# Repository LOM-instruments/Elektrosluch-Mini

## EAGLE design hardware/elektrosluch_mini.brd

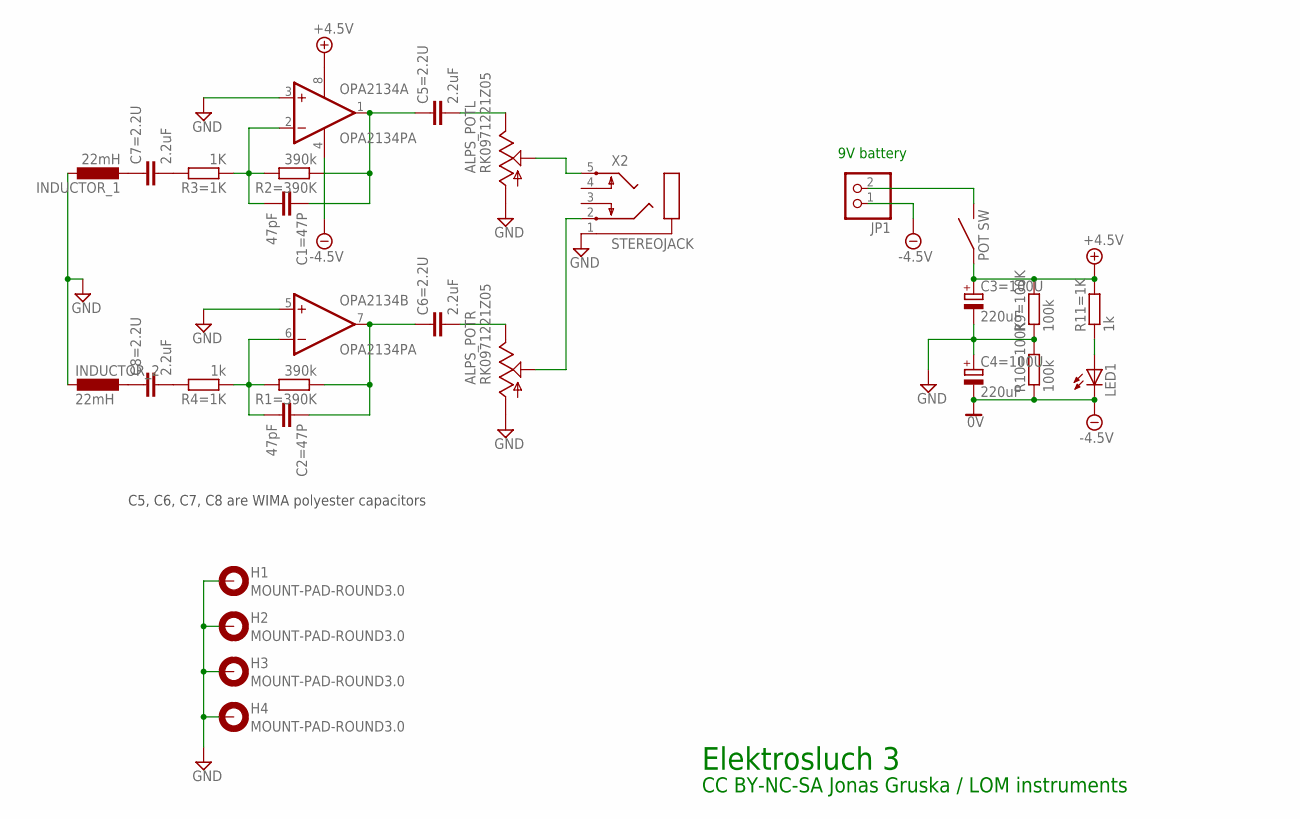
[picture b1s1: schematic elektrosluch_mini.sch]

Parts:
ALPS_POT: RK0971221Z05; ALPS_RK0971221Z0X
C1=47P, C2=47P: 47pF; C050-024X044
C3=100U, C4=100U: 220uF; E2,5-5
C5=2.2U, C6=2.2U, C7=2.2U, C8=2.2U: 2.2uF; WIMA10UF
H1, H2, H3, H4: MOUNT-PAD-ROUND3.0; 3,0-PAD
INDUCTOR_1, INDUCTOR_2: 22mH; COIL
JP1: PINHD-1X2; 1X02
LED1: LED3MM
OPA2134: OPA2134PA; DIL08
R1=390K, R2=390K: 390k; 0207/10
R3=1K: 1K; 0207/10
R4=1K, R11=1K: 1k; 0207/10
R9=100K, R10=100K: 100k; 0207/10
X2: STEREOJACK; STX3100

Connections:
+5V: ALPS_POT.S1, C3=100U.+, OPA2134.8 (V+), R9=100K.2, R11=1K.2
-5V: C4=100U.-, JP1.1, LED1.K (C), OPA2134.4 (V-), R10=100K.1
GND: ALPS_POT.G1 (1), ALPS_POT.G2 (1), C3=100U.-, C4=100U.+, H1.B3,0, H2.B3,0, H3.B3,0, H4.B3,0, INDUCTOR_1.P$1 (1), INDUCTOR_2.P$2 (2), OPA2134.3 (+IN), OPA2134.5 (+IN), R9=100K.1, R10=100K.2, X2.1
unnamed: C1=47P.2, OPA2134.2 (-IN), R2=390K.2, R3=1K.1
unnamed: C1=47P.1, C5=2.2U.P$1 (1), OPA2134.1 (OUT), R2=390K.1
unnamed: ALPS_POT.I1 (3), C5=2.2U.P$2 (2)
unnamed: C2=47P.2, OPA2134.6 (-IN), R1=390K.2, R4=1K.1
unnamed: C2=47P.1, C6=2.2U.P$1 (1), OPA2134.7 (OUT), R1=390K.1
unnamed: ALPS_POT.I2 (3), C6=2.2U.P$2 (2)
unnamed: ALPS_POT.O1 (2), X2.5
unnamed: C7=2.2U.P$1 (1), INDUCTOR_1.P$2 (2)
unnamed: ALPS_POT.O2 (2), X2.2
unnamed: C8=2.2U.P$1 (1), INDUCTOR_2.P$1 (1)
unnamed: C7=2.2U.P$2 (2), R3=1K.2
unnamed: LED1.A, R11=1K.1
unnamed: C8=2.2U.P$2 (2), R4=1K.2
unnamed: ALPS_POT.S2, JP1.2

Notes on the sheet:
9V battery
Elektrosluch 3
CC BY-NC-SA Jonas Gruska / LOM instruments
C5, C6, C7, C8 are WIMA polyester capacitors

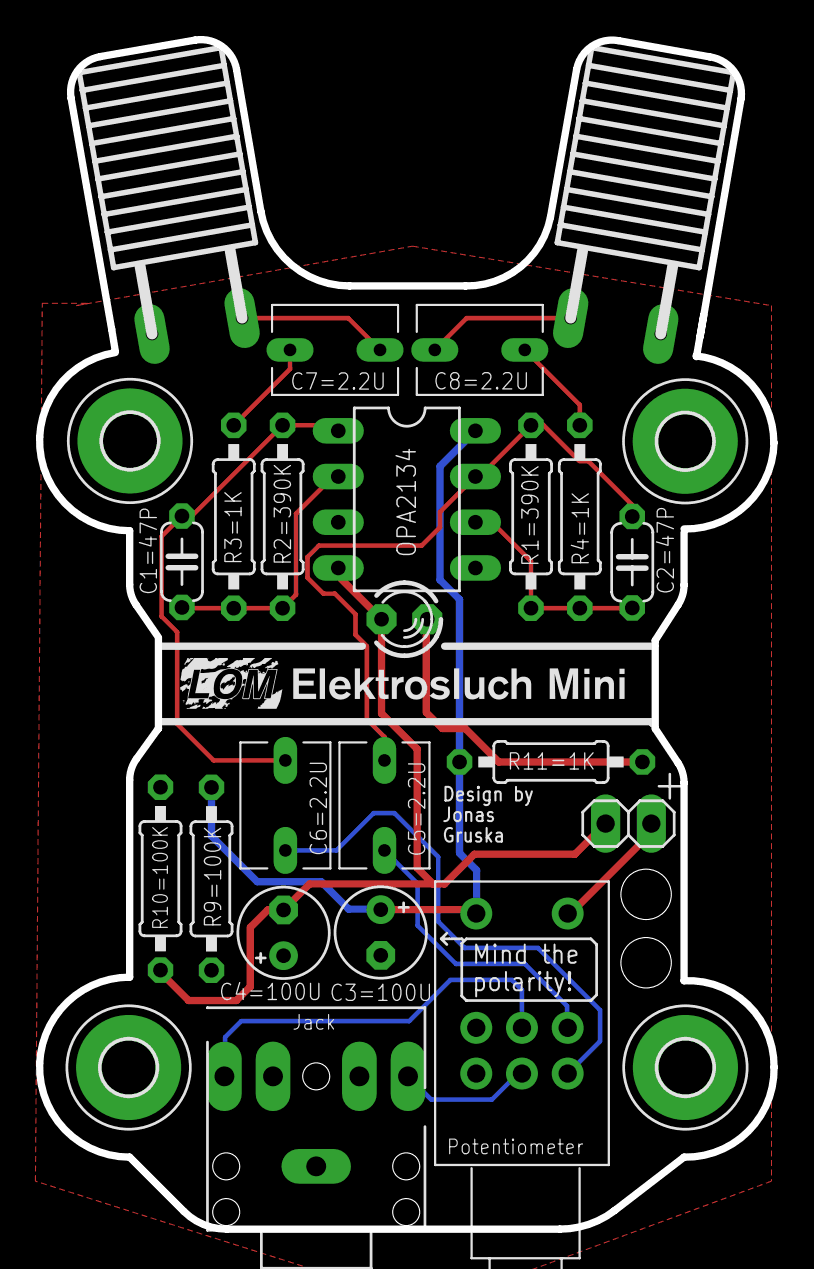
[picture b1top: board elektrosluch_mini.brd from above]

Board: 2 copper layers, 40.8 x 66.1 mm, 27 parts (0 on the bottom side), 17 nets.

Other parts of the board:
U$1: ELEKTROSLUCHMINI

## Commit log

2016-04-10 first
2016-04-10 photos
2016-04-10 photos2
2016-04-10 photos3
2016-04-10 photos4
2016-04-11 photos5
